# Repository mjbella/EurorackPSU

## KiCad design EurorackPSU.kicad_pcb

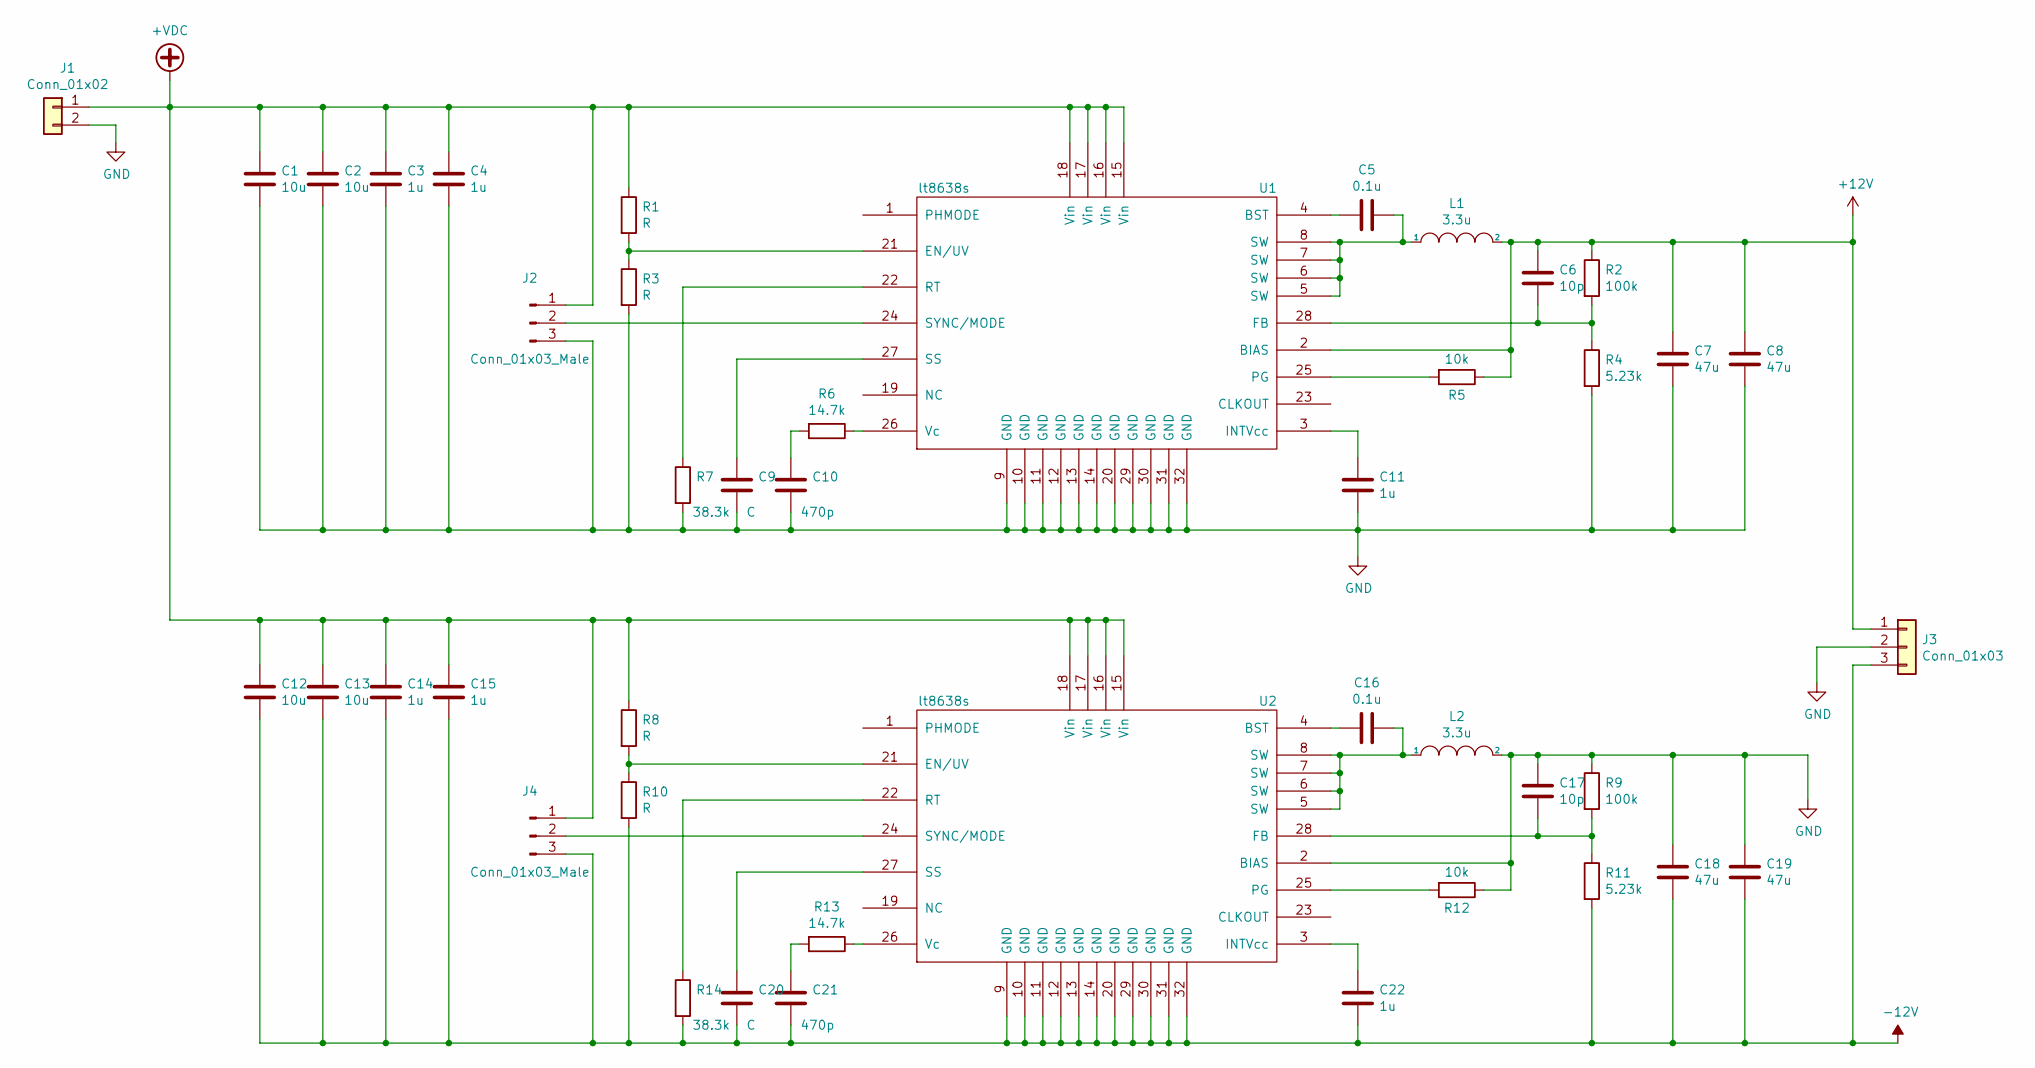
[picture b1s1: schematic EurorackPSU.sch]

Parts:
C1, C2, C12, C13: 10u; C_1210_3225Metric
C3, C4, C11, C14, C15, C22: 1u; C_0603_1608Metric
C5, C16: 0.1u; C_0603_1608Metric
C6, C17: 10p; C_0603_1608Metric
C7, C8, C18, C19: 47u; C_1210_3225Metric
C9, C20: C; C_0603_1608Metric
C10, C21: 470p; C_0603_1608Metric
J1: Conn_01x02; Molex_Mini-Fit_Sr_42819-22XX_1x02_P10.00mm_Vertical
J2, J4: Conn_01x03_Male; PinHeader_1x03_P2.54mm_Vertical
J3: Conn_01x03; Molex_Mini-Fit_Sr_42819-32XX_1x03_P10.00mm_Vertical
L1, L2: 3.3u; L_Coilcraft_XAL60xx_6.36x6.56mm
R1, R3, R8, R10: R; R_0603_1608Metric
R2, R9: 100k; R_0603_1608Metric
R4, R11: 5.23k; R_0603_1608Metric
R5, R12: 10k; R_0603_1608Metric
R6, R13: 14.7k; R_0603_1608Metric
R7, R14: 38.3k; R_0603_1608Metric
U1, U2: lt8638s; LQFN-28_5x4mm_0.94mm

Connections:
+12V: C6.1, C7.1, C8.1, J3.1, L1.2, R2.1, R5.1, U1.2 (BIAS)
+VDC: C1.1, C2.1, C3.1, C4.1, C12.1, C13.1, C14.1, C15.1, J1.1, J2.1, J4.1, R1.1, R8.1, U1.15 (Vin), U1.16 (Vin), U1.17 (Vin), U1.18 (Vin), U2.15 (Vin), U2.16 (Vin), U2.17 (Vin), U2.18 (Vin)
-12V: C12.2, C13.2, C14.2, C15.2, C18.2, C19.2, C20.2, C21.2, C22.2, J3.3, J4.3, R10.2, R11.2, R14.2, U2.9 (GND), U2.10 (GND), U2.11 (GND), U2.12 (GND), U2.13 (GND), U2.14 (GND), U2.20 (GND), U2.29 (GND), U2.30 (GND), U2.31 (GND), U2.32 (GND)
GND: C1.2, C2.2, C3.2, C4.2, C7.2, C8.2, C9.2, C10.2, C11.2, C17.1, C18.1, C19.1, J1.2, J2.3, J3.2, L2.2, R3.2, R4.2, R7.2, R9.1, R12.1, U1.9 (GND), U1.10 (GND), U1.11 (GND), U1.12 (GND), U1.13 (GND), U1.14 (GND), U1.20 (GND), U1.29 (GND), U1.30 (GND), U1.31 (GND), U1.32 (GND), U2.2 (BIAS)
unnamed: C5.1, L1.1, U1.5 (SW), U1.6 (SW), U1.7 (SW), U1.8 (SW)
unnamed: C5.2, U1.4 (BST)
unnamed: C6.2, R2.2, R4.1, U1.28 (FB)
unnamed: C9.1, U1.27 (SS)
unnamed: C10.1, R6.2
unnamed: C11.1, U1.3 (INTVcc)
unnamed: C16.1, L2.1, U2.5 (SW), U2.6 (SW), U2.7 (SW), U2.8 (SW)
unnamed: C16.2, U2.4 (BST)
unnamed: C17.2, R9.2, R11.1, U2.28 (FB)
unnamed: C20.1, U2.27 (SS)
unnamed: C21.1, R13.2
unnamed: C22.1, U2.3 (INTVcc)
unnamed: J2.2, U1.24 (SYNC/MODE)
unnamed: J4.2, U2.24 (SYNC/MODE)
unnamed: R1.2, R3.1, U1.21 (EN/UV)
unnamed: R5.2, U1.25 (PG)
unnamed: R6.1, U1.26 (Vc)
unnamed: R7.1, U1.22 (RT)
unnamed: R8.2, R10.1, U2.21 (EN/UV)
unnamed: R12.2, U2.25 (PG)
unnamed: R13.1, U2.26 (Vc)
unnamed: R14.1, U2.22 (RT)

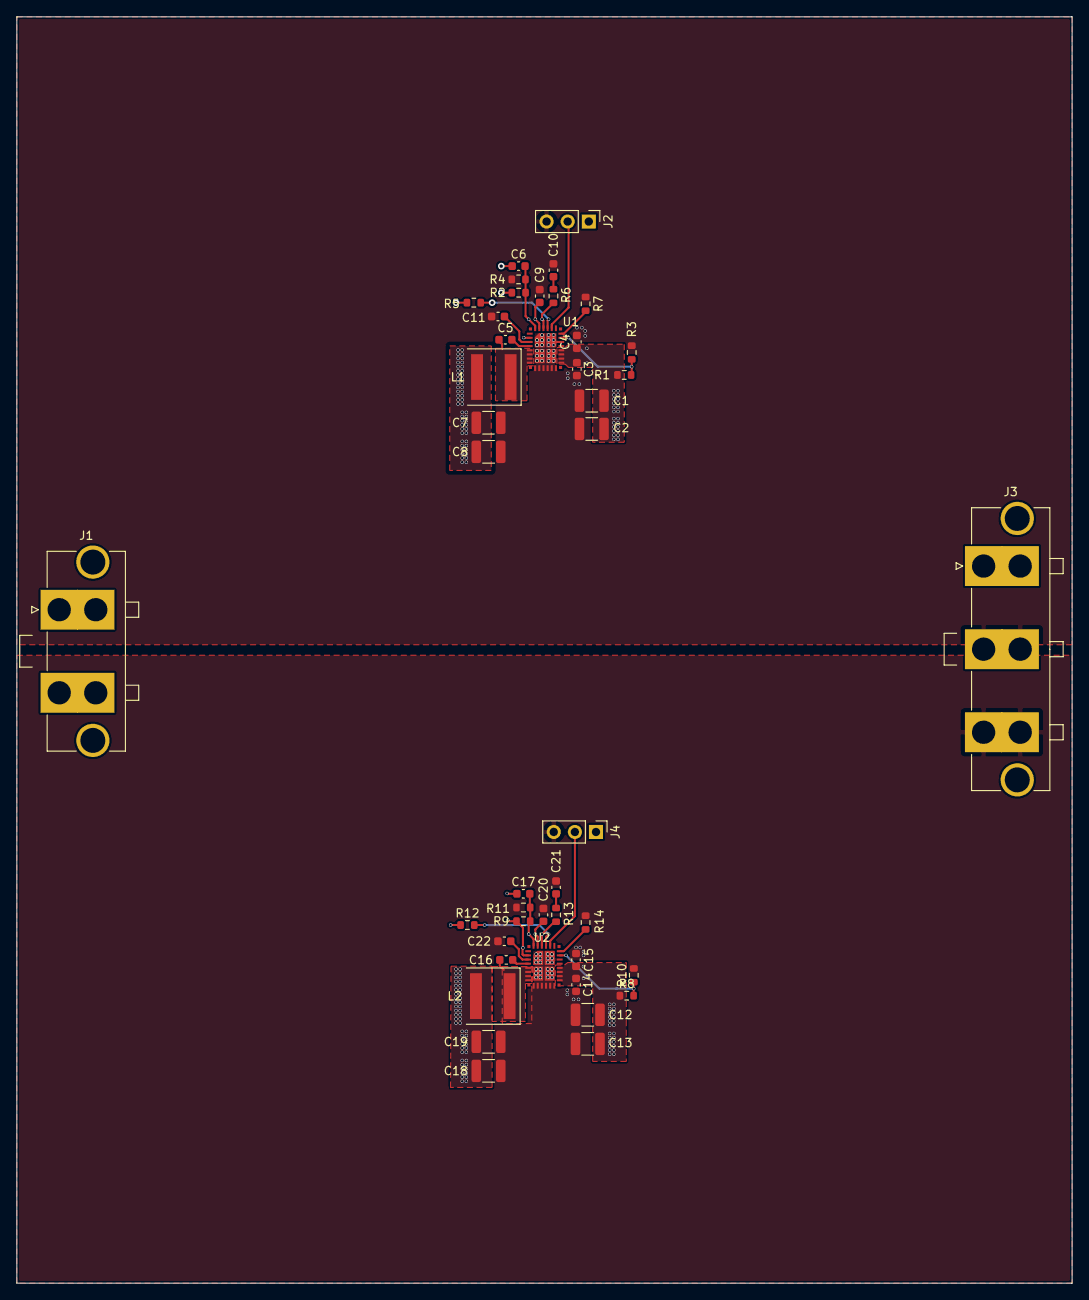
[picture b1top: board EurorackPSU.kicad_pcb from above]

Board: 4 copper layers, 127.0 x 152.4 mm, 44 parts (0 on the bottom side), 26 nets.

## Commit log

2021-06-11 Routing signals for the +12v regulator
2021-06-11 Routing signals for the -12v regulator
2021-06-11 More signal routing
2021-06-12 Assigned connectors for power input and output, and exported the netlist again
2021-06-12 Initial connector placement and more power plane setup
2021-06-13 Added net name for power input, added more vias, and more
